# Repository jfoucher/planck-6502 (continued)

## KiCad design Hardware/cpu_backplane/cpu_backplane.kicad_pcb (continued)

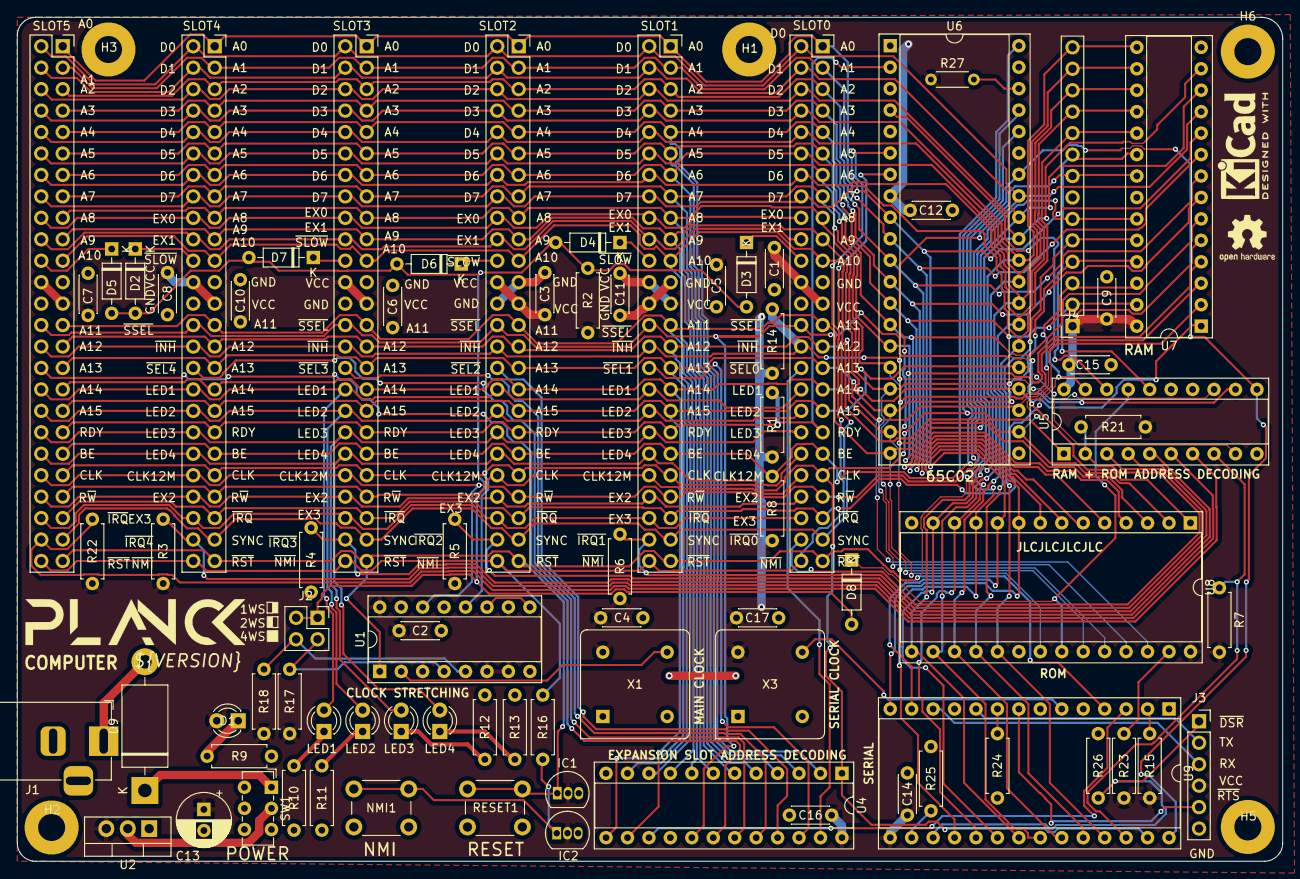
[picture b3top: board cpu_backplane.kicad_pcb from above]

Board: 2 copper layers, 149.9 x 99.9 mm, 85 parts (0 on the bottom side), 92 nets.

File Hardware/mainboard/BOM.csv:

Ref;Qnty;Value;Cmp name;Footprint;Description;Vendor
C1, C3, C7, C8, C10, C11,;6;1u;C_Small;Capacitor_THT:C_Disc_D4.3mm_W1.9mm_P5.00mm;Unpolarized capacitor, small symbol;
C2, C4, C5, C9, C12, C14, C15, C16, C17,;9;10n;C_Small;Capacitor_THT:C_Disc_D4.3mm_W1.9mm_P5.00mm;Unpolarized capacitor, small symbol;
C6,;1;47n;C_Small;Capacitor_THT:C_Disc_D4.3mm_W1.9mm_P5.00mm;Unpolarized capacitor, small symbol;
C13,;1;47u;C_Small;Capacitor_THT:CP_Radial_D6.3mm_P2.50mm;Unpolarized capacitor, small symbol;
D1,;1;LED;LED;LED_THT:LED_D3.0mm;Light emitting diode;
D2, D3, D4, D5, D6, D7, D8,;7;1N4148;D;Diode_THT:D_DO-35_SOD27_P7.62mm_Horizontal;Diode;
H1, H2, H3, H5, H6,;5;MountingHole_Pad;MountingHole_Pad;MountingHole:MountingHole_3.2mm_M3_Pad;Mounting Hole with connection;
J1,;1;USB_B_Micro;USB_B_Micro-Connector;Connector_USB:USB_Micro-B_Molex-105017-0001;;
J2,;1;Conn_02x02_Odd_Even;Conn_02x02_Odd_Even;Connector_PinHeader_2.54mm:PinHeader_2x02_P2.54mm_Vertical;Generic connector, double row, 02x02, odd/even pin numbering scheme (row 1 odd numbers, row 2 even numbers), script generated (kicad-library-utils/schlib/autogen/connector/);
J3,;1;Conn_01x06;Conn_01x06;Connector_PinSocket_2.54mm:PinSocket_1x06_P2.54mm_Vertical;Generic connector, single row, 01x06, script generated (kicad-library-utils/schlib/autogen/connector/);
J4,;1;Conn_01x14;Conn_01x14;Connector_PinSocket_2.54mm:PinSocket_1x14_P2.54mm_Vertical;Generic connector, single row, 01x14, script generated (kicad-library-utils/schlib/autogen/connector/);
LED1, LED2, LED3, LED4,;4;LED;LED;LED_THT:LED_D3.0mm;Light emitting diode;
NMI1,;1;SW_Push;SW_Push;Button_Switch_THT:SW_PUSH_6mm;Push button switch, generic, two pins;
R1, R8, R15, R23, R24, R25, R26,;7;10k;R_Small;Resistor_THT:R_Axial_DIN0207_L6.3mm_D2.5mm_P7.62mm_Horizontal;Resistor, small symbol;
R2, R3, R4, R5, R6, R14, R17, R18, R21, R22,;10;1k;R_Small;Resistor_THT:R_Axial_DIN0207_L6.3mm_D2.5mm_P7.62mm_Horizontal;Resistor, small symbol;
R9, R10, R11, R12, R13,;5;470R;R_Small;Resistor_THT:R_Axial_DIN0207_L6.3mm_D2.5mm_P7.62mm_Horizontal;Resistor, small symbol;
R16,;1;4.7k;R_Small;Resistor_THT:R_Axial_DIN0207_L6.3mm_D2.5mm_P7.62mm_Horizontal;Resistor, small symbol;
R27,;1;10k;R_Small;Resistor_THT:R_Axial_DIN0204_L3.6mm_D1.6mm_P5.08mm_Horizontal;Resistor, small symbol;
RESET1,;1;SW_Push;SW_Push;Button_Switch_THT:SW_PUSH_6mm;Push button switch, generic, two pins;
SLOT0, SLOT1, SLOT2, SLOT3, SLOT4, SLOT5,;6;Conn_01x40;Conn_02x25_Odd_Even;Connector_PinSocket_2.54mm:PinSocket_2x25_P2.54mm_Vertical;Generic connector, double row, 02x25, odd/even pin numbering scheme (row 1 odd numbers, row 2 even numbers), script generated (kicad-library-utils/schlib/autogen/connector/);
SW1,;1;SW_SPST;SW_SPST;Button_Switch_THT:SW_E-Switch_EG1271_DPDT;Single Pole Single Throw (SPST) switch;
U1,;1;74AC161;74LS161;Package_DIP:DIP-16_W7.62mm_Socket;Synchronous 4-bit programmable binary Counter;
U2, U3,;2;MAX811SEUS-T;MAX811SEUS-T;Package_TO_SOT_SMD:SOT-143;Power supply supervisor, Manual reset, Threshold 2.93V, SOT-143;
U4,;1;PAL24;PAL24;Package_DIP:DIP-24_W7.62mm_Socket;generic 24-pin Programmable Array Logic (PAL) device;
U5,;1;GAL16V8;GAL16V8;Package_DIP:DIP-20_W7.62mm_Socket;Programmable Logic Array, DIP-20/SOIC-20/PLCC-20;
U6,;1;W65C02SxP;W65C02SxP;Package_DIP:DIP-40_W15.24mm_Socket;W65C02S 8-bit CMOS General Purpose Microprocessor, DIP-40;
U7,;1;HM62256BLP;HM62256BLP;Package_DIP:DIP-28_W7.62mm_Socket;32,768-word × 8-bit High Speed CMOS Static RAM, 70ns, DIP-28;
U8,;1;28C256;28C256;Package_DIP:DIP-28_W15.24mm_Socket;Paged Parallel EEPROM 256Kb (32K x 8), DIP-28/SOIC-28;
U9,;1;W65C51NxP;W65C51NxP;Package_DIP:DIP-28_W15.24mm_Socket;W65C51N CMOS Asynchronous Communication Interface Adapter (ACIA), Serial UART, DIP-28;
X1,;1;24MHz;CXO_DIP8;Oscillator:Oscillator_DIP-8;Crystal Clock Oscillator, DIP8-style metal package;
X3,;1;1.8432MHz;CXO_DIP8;Oscillator:Oscillator_DIP-8;Crystal Clock Oscillator, DIP8-style metal package;

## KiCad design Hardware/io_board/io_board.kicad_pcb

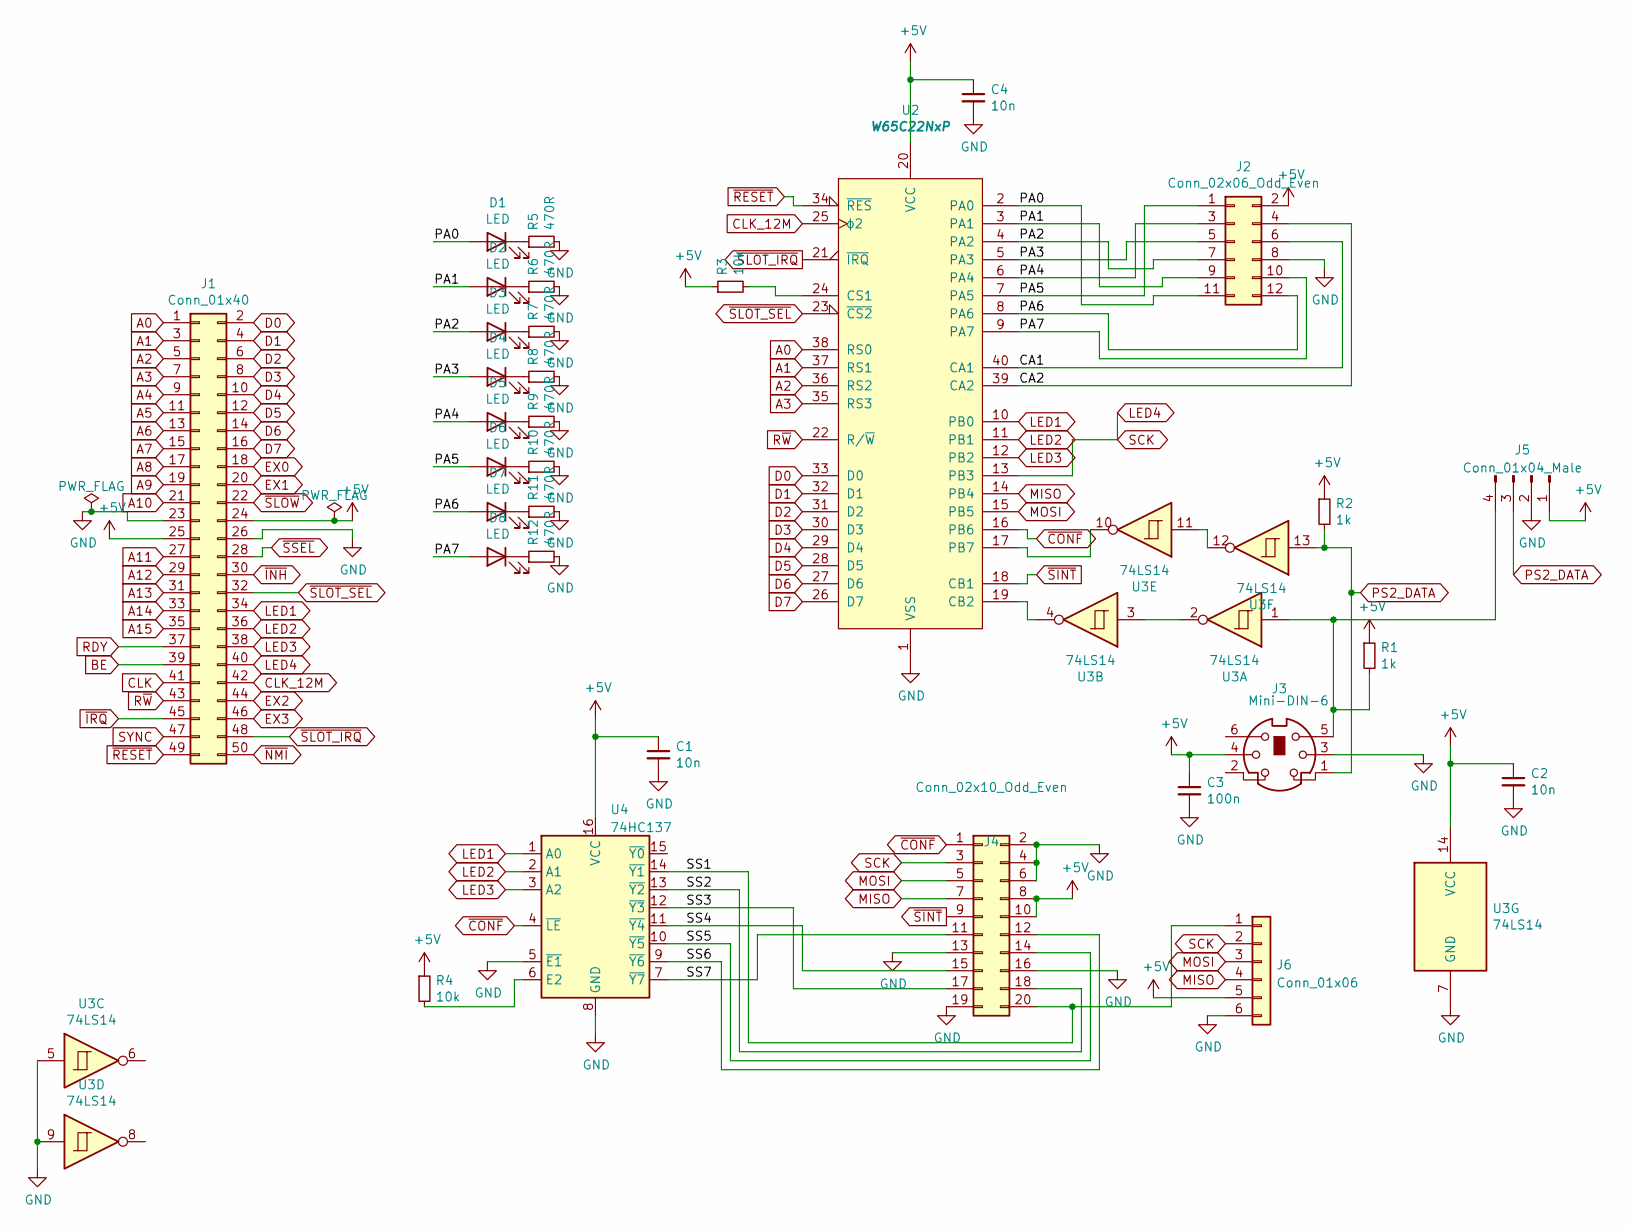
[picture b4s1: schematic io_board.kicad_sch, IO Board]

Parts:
C1, C2, C4: 10n; C_Disc_D4.7mm_W2.5mm_P5.00mm
C3: 100n; C_Disc_D4.7mm_W2.5mm_P5.00mm
D1, D2, D3, D4, D5, D6, D7, D8: LED; LED_D3.0mm_Horizontal_O3.81mm_Z6.0mm_2
J1: Conn_01x40; PinHeader_2x25_P2.54mm_Horizontal
J2: Conn_02x06_Odd_Even; PinHeader_2x06_P2.54mm_Horizontal
J3: Mini-DIN-6; Connector_Mini-DIN_Female_6Pin_2rows
J4: Conn_02x10_Odd_Even; PinHeader_2x10_P2.54mm_Horizontal
J5: Conn_01x04_Male; PinHeader_1x04_P2.54mm_Vertical
J6: Conn_01x06; PinSocket_1x06_P2.54mm_Vertical
R1, R2: 1k; R_Axial_DIN0207_L6.3mm_D2.5mm_P7.62mm_Horizontal
R3, R4: 10k; R_Axial_DIN0207_L6.3mm_D2.5mm_P7.62mm_Horizontal
R5, R6, R7, R8, R9, R10, R11, R12: 470R; R_Axial_DIN0207_L6.3mm_D2.5mm_P7.62mm_Horizontal
U2: W65C22NxP; DIP-40_W15.24mm_Socket
U3: 74LS14; DIP-14_W7.62mm_Socket
U4: 74HC137; DIP-16_W7.62mm_Socket

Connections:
+5V: C1.1, C2.1, C3.1, C4.1, J1.24, J1.25, J2.2, J3.4, J4.8, J4.10, J5.1, J6.5, R1.1, R2.1, R3.1, R4.1, U2.20 (VCC), U3.14 (VCC), U4.16 (VCC)
/CA1: J2.6, U2.40 (CA1)
/CA2: J2.4, U2.39 (CA2)
/PA0: D1.2 (A), J2.11, U2.2 (PA0)
/PA1: D2.2 (A), J2.9, U2.3 (PA1)
/PA2: D3.2 (A), J2.7, U2.4 (PA2)
/PA3: D4.2 (A), J2.5, U2.5 (PA3)
/PA4: D5.2 (A), J2.3, U2.6 (PA4)
/PA5: D6.2 (A), J2.1, U2.7 (PA5)
/PA6: D7.2 (A), J2.12, U2.8 (PA6)
/PA7: D8.2 (A), J2.10, U2.9 (PA7)
/SS1: J4.20, J6.1, U4.14 (~Y1)
/SS2: J4.18, U4.13 (~Y2)
/SS3: J4.17, U4.12 (~Y3)
/SS4: J4.15, U4.11 (~Y4)
/SS5: J4.14, U4.10 (~Y5)
/SS6: J4.12, U4.9 (~Y6)
/SS7: J4.11, U4.7 (~Y7)
A0: J1.1, U2.38 (RS0)
A1: J1.3, U2.37 (RS1)
A2: J1.5, U2.36 (RS2)
A3: J1.7, U2.35 (RS3)
A4: J1.9
A5: J1.11
A6: J1.13
A7: J1.15
A8: J1.17
A9: J1.19
A10: J1.21
A11: J1.27
A12: J1.29
A13: J1.31
A14: J1.33
A15: J1.35
BE: J1.39
CLK: J1.41
CLK_12M: J1.42, U2.25 (ϕ2)
D0: J1.2, U2.33 (D0)
D1: J1.4, U2.32 (D1)
D2: J1.6, U2.31 (D2)
D3: J1.8, U2.30 (D3)
D4: J1.10, U2.29 (D4)
D5: J1.12, U2.28 (D5)
D6: J1.14, U2.27 (D6)
D7: J1.16, U2.26 (D7)
EX0: J1.18
EX1: J1.20
EX2: J1.44
EX3: J1.46
GND: C1.2, C2.2, C3.2, C4.2, J1.23, J1.26, J2.8, J3.3, J4.2, J4.4, J4.6, J4.13, J4.16, J4.19, J5.2, J6.6, R5.2, R6.2, R7.2, R8.2, R9.2, R10.2, R11.2, R12.2, U2.1 (VSS), U3.5, U3.7 (GND), U3.9, U4.5 (~E1), U4.8 (GND)
LED1: J1.34, U2.10 (PB0), U4.1 (A0)
LED2: J1.36, U2.11 (PB1), U4.2 (A1)
LED3: J1.38, U2.12 (PB2), U4.3 (A2)
LED4: J1.40, J4.3, J6.2, U2.13 (PB3)
MISO: J4.7, J6.4, U2.14 (PB4)
MOSI: J4.5, J6.3, U2.15 (PB5)
unnamed: D1.1 (K), R5.1
unnamed: D2.1 (K), R6.1
unnamed: D3.1 (K), R7.1
unnamed: D4.1 (K), R8.1
unnamed: D5.1 (K), R9.1
unnamed: D6.1 (K), R10.1
unnamed: D7.1 (K), R11.1
unnamed: D8.1 (K), R12.1
unnamed: J3.5, J5.4, R1.2, U3.1
unnamed: R3.2, U2.24 (CS1)
unnamed: R4.2, U4.6 (E2)
unnamed: U2.17 (PB7), U3.10
unnamed: U2.19 (CB2), U3.4
unnamed: U3.2, U3.3
unnamed: U3.11, U3.12
PS2_DATA: J3.1, J5.3, R2.2, U3.13
RDY: J1.37
R~W: J1.43, U2.22 (R/~W)
SYNC: J1.47
~CONF: J4.1, U2.16 (PB6), U4.4 (~LE)
~INH: J1.30
~IRQ: J1.45
~NMI: J1.50
~RESET: J1.49, U2.34 (~RES)
~SINT: J4.9, U2.18 (CB1)
~SLOT_IRQ: J1.48, U2.21 (~IRQ)
~SLOT_SEL: J1.32, U2.23 (~CS2)
~SLOW: J1.22
~SSEL: J1.28

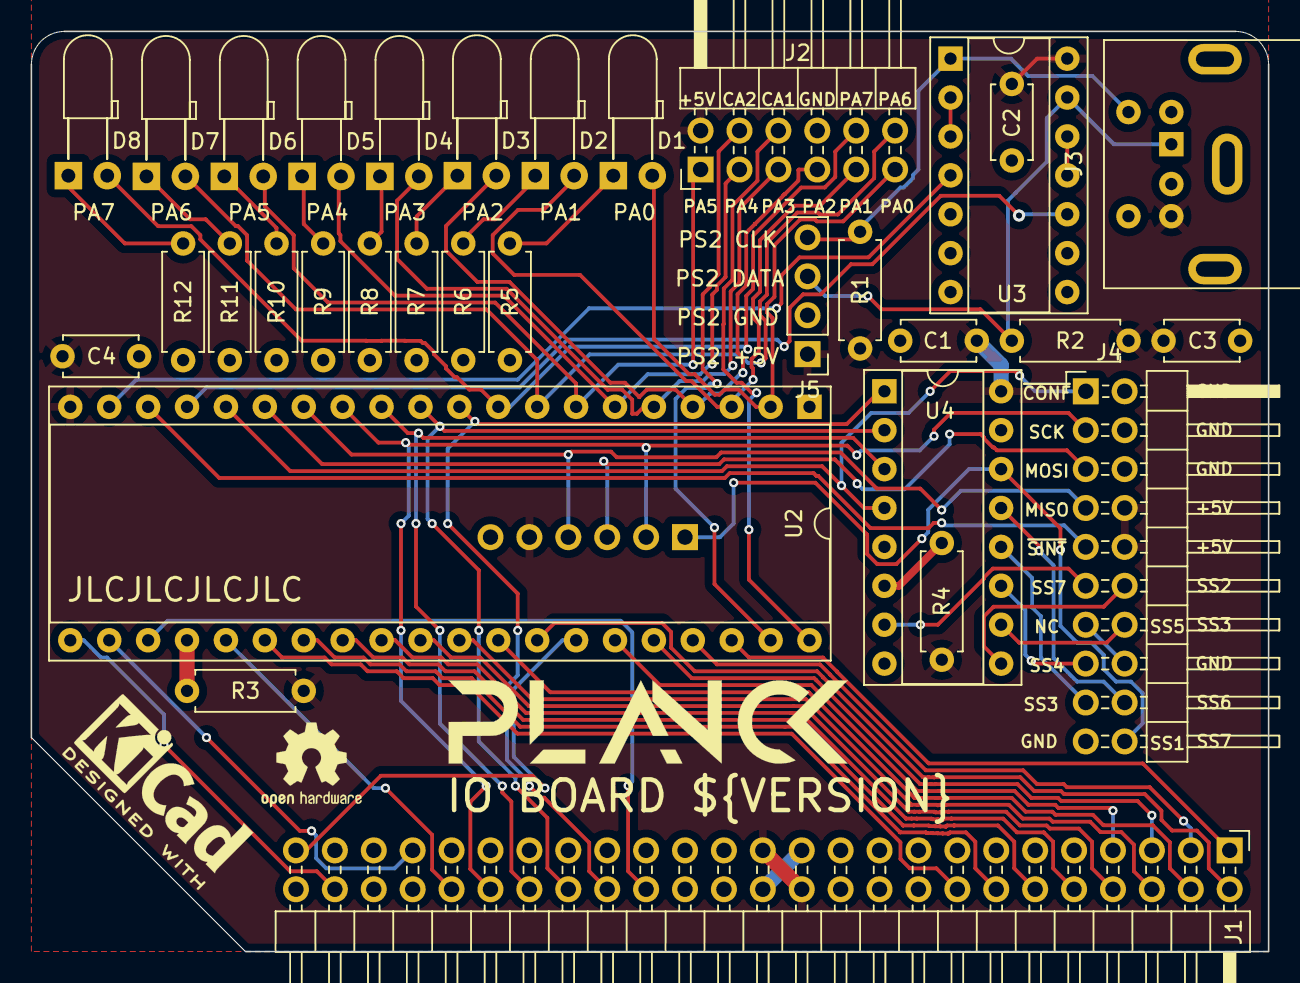
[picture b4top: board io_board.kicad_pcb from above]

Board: 2 copper layers, 80.8 x 60.1 mm, 33 parts (1 on the bottom side), 60 nets.

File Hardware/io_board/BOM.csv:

Ref;Qnty;Value;Cmp name;Footprint;Description;Vendor
C1, C2, C4,;3;10n;C_Small;Capacitor_THT:C_Disc_D4.7mm_W2.5mm_P5.00mm;Unpolarized capacitor, small symbol;
C3,;1;100n;C_Small;Capacitor_THT:C_Disc_D4.7mm_W2.5mm_P5.00mm;Unpolarized capacitor, small symbol;
D1, D2, D3, D4, D5, D6, D7, D8,;8;LED;LED;LED_THT:LED_D3.0mm_Horizontal_O3.81mm_Z6.0mm;Light emitting diode;
J1,;1;Conn_01x40;Conn_02x25_Odd_Even;Connector_PinHeader_2.54mm:PinHeader_2x25_P2.54mm_Horizontal;Generic connector, double row, 02x25, odd/even pin numbering scheme (row 1 odd numbers, row 2 even numbers);
J2,;1;Conn_02x06_Odd_Even;Conn_02x06_Odd_Even;Connector_PinHeader_2.54mm:PinHeader_2x06_P2.54mm_Horizontal;Generic connector, double row, 02x06, odd/even pin numbering scheme (row 1 odd numbers, row 2 even numbers);
J3,;1;Mini-DIN-6;Mini-DIN-6;mini-din:MINI-DIN-6-FULL-SHIELD;6-pin Mini-DIN connector;
J4,;1;Conn_02x10_Odd_Even;Conn_02x10_Odd_Even;Connector_PinHeader_2.54mm:PinHeader_2x10_P2.54mm_Horizontal;Generic connector, double row, 02x10, odd/even pin numbering scheme (row 1 odd numbers, row 2 even numbers);
R1, R2,;2;1k;R_Small;Resistor_THT:R_Axial_DIN0207_L6.3mm_D2.5mm_P7.62mm_Horizontal;Resistor, small symbol;
R3, R4,;2;10k;R_Small;Resistor_THT:R_Axial_DIN0207_L6.3mm_D2.5mm_P7.62mm_Horizontal;Resistor, small symbol;
R5, R6, R7, R8, R9, R10, R11, R12,;8;470R;R_Small;Resistor_THT:R_Axial_DIN0207_L6.3mm_D2.5mm_P7.62mm_Horizontal;Resistor, small symbol;
U1,;1;74LS138;74LS138;Package_DIP:DIP-16_W7.62mm_Socket;Decoder 3 to 8 active low outputs;
U2,;1;W65C22NxP;W65C22NxP;Package_DIP:DIP-40_W15.24mm_Socket;W65C22N CMOS Versatile Interface Adapter (VIA), 20-pin I/O, 2 Timer/Counters, NMOS-Compatible, DIP-40;
U3,;1;74LS14;74LS14;Package_DIP:DIP-14_W7.62mm_Socket;Hex inverter schmitt trigger;

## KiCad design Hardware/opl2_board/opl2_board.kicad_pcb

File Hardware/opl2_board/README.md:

## Planck 6502 sound card

This is a sound card based on the YM3892 OPL2 sound chip.

You can [download the schematic](https://planck6502.com/fabrication/opl2_board-schematic.pdf) and the [gerber files](https://planck6502.com/fabrication/opl2_board-zip.zip)

[Documentation](https://planck6502.com/Hardware/opl2/)

<br />This documentation is licensed under a <a rel="license" href="http://creativecommons.org/licenses/by-sa/4.0/">Creative Commons Attribution-ShareAlike 4.0 International License</a>.

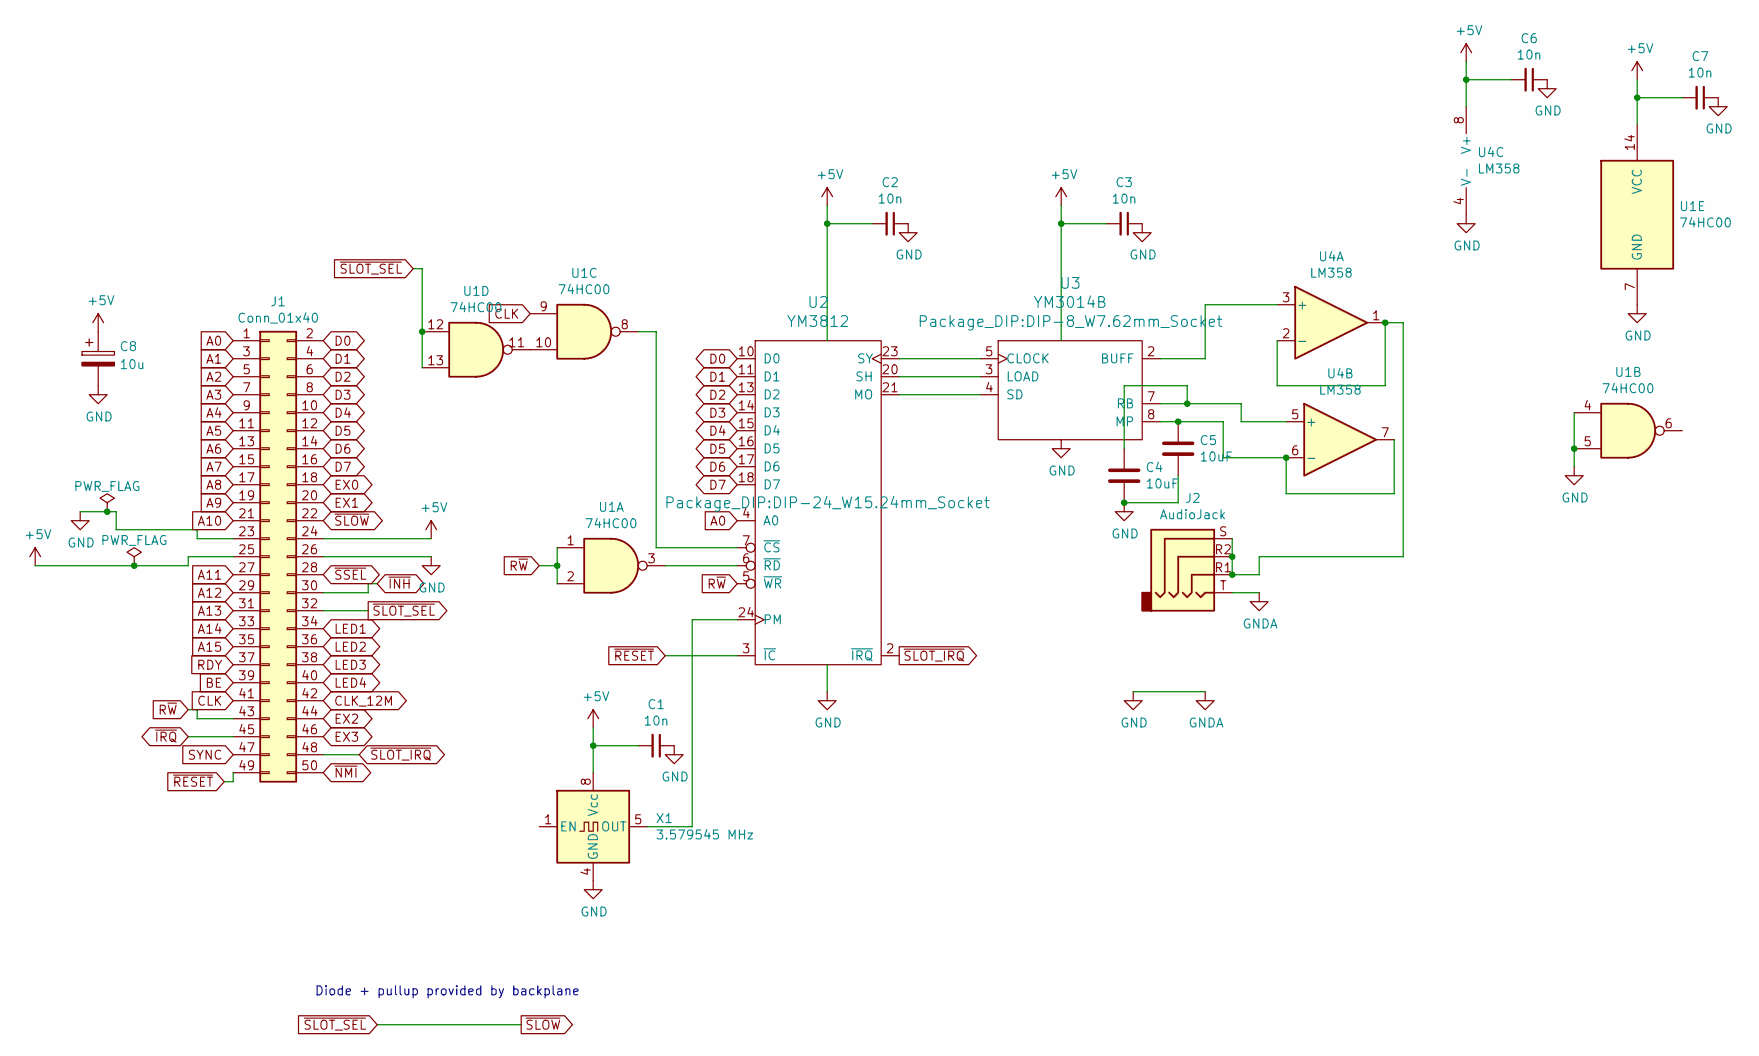
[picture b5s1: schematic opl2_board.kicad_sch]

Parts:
C1, C2, C3, C6, C7: 10n; C_Disc_D4.3mm_W1.9mm_P5.00mm
C4, C5: 10uF; C_Disc_D4.3mm_W1.9mm_P5.00mm
C8: 10u; CP_Radial_D5.0mm_P2.50mm
J1: Conn_01x40; PinHeader_2x25_P2.54mm_Horizontal
J2: AudioJack; TRRS-PJ-320A-no-Fmask
U1: 74HC00; DIP-14_W7.62mm_Socket
U2: YM3812; DIP-24_W15.24mm_Socket
U3: YM3014B; DIP-8_W7.62mm_Socket
U4: LM358; DIP-8_W7.62mm_Socket
X1: 3.579545 MHz; Oscillator_DIP-8

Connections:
+5V: C1.2, C2.2, C3.2, C6.2, C7.2, C8.1, J1.24, J1.25, U1.14 (VCC), U2.1 (VCC), U3.1 (VCC), U4.8 (V+), X1.8 (Vcc)
A0: J1.1, U2.4 (A0)
A1: J1.3
A2: J1.5
A3: J1.7
A4: J1.9
A5: J1.11
A6: J1.13
A7: J1.15
A8: J1.17
A9: J1.19
A10: J1.21
A11: J1.27
A12: J1.29
A13: J1.31
A14: J1.33
A15: J1.35
BE: J1.39
CLK: J1.41, U1.9
CLK_12M: J1.42
D0: J1.2, U2.10 (D0)
D1: J1.4, U2.11 (D1)
D2: J1.6, U2.13 (D2)
D3: J1.8, U2.14 (D3)
D4: J1.10, U2.15 (D4)
D5: J1.12, U2.16 (D5)
D6: J1.14, U2.17 (D6)
D7: J1.16, U2.18 (D7)
EX0: J1.18
EX1: J1.20
EX2: J1.44
EX3: J1.46
GND: C1.1, C2.1, C3.1, C4.2, C5.2, C6.1, C7.1, C8.2, J1.23, J1.26, J2.T, U1.4, U1.5, U1.7 (GND), U2.12 (GND), U3.6 (GND), U4.4 (V-), X1.4 (GND)
LED1: J1.34
LED2: J1.36
LED3: J1.38
LED4: J1.40
unnamed: C4.1, U3.7 (RB), U4.5 (+)
unnamed: C5.1, U3.8 (MP), U4.6 (-), U4.7
unnamed: J2.R1, J2.R2, J2.S, U4.1, U4.2 (-)
unnamed: U1.3, U2.6 (~RD)
unnamed: U1.8, U2.7 (~CS)
unnamed: U1.10, U1.11
unnamed: U2.20 (SH), U3.3 (LOAD)
unnamed: U2.21 (MO), U3.4 (SD)
unnamed: U2.23 (SY), U3.5 (CLOCK)
unnamed: U2.24 (PM), X1.5 (OUT)
unnamed: U3.2 (BUFF), U4.3 (+)
RDY: J1.37
R~W: J1.43, U1.1, U1.2, U2.5 (~WR)
SYNC: J1.47
~INH: J1.30
~IRQ: J1.45
~NMI: J1.50
~RESET: J1.49, U2.3 (~IC)
~SLOT_IRQ: J1.48, U2.2 (~IRQ)
~SLOT_SEL: J1.22, J1.32, U1.12, U1.13
~SSEL: J1.28

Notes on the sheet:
Diode + pullup provided by backplane

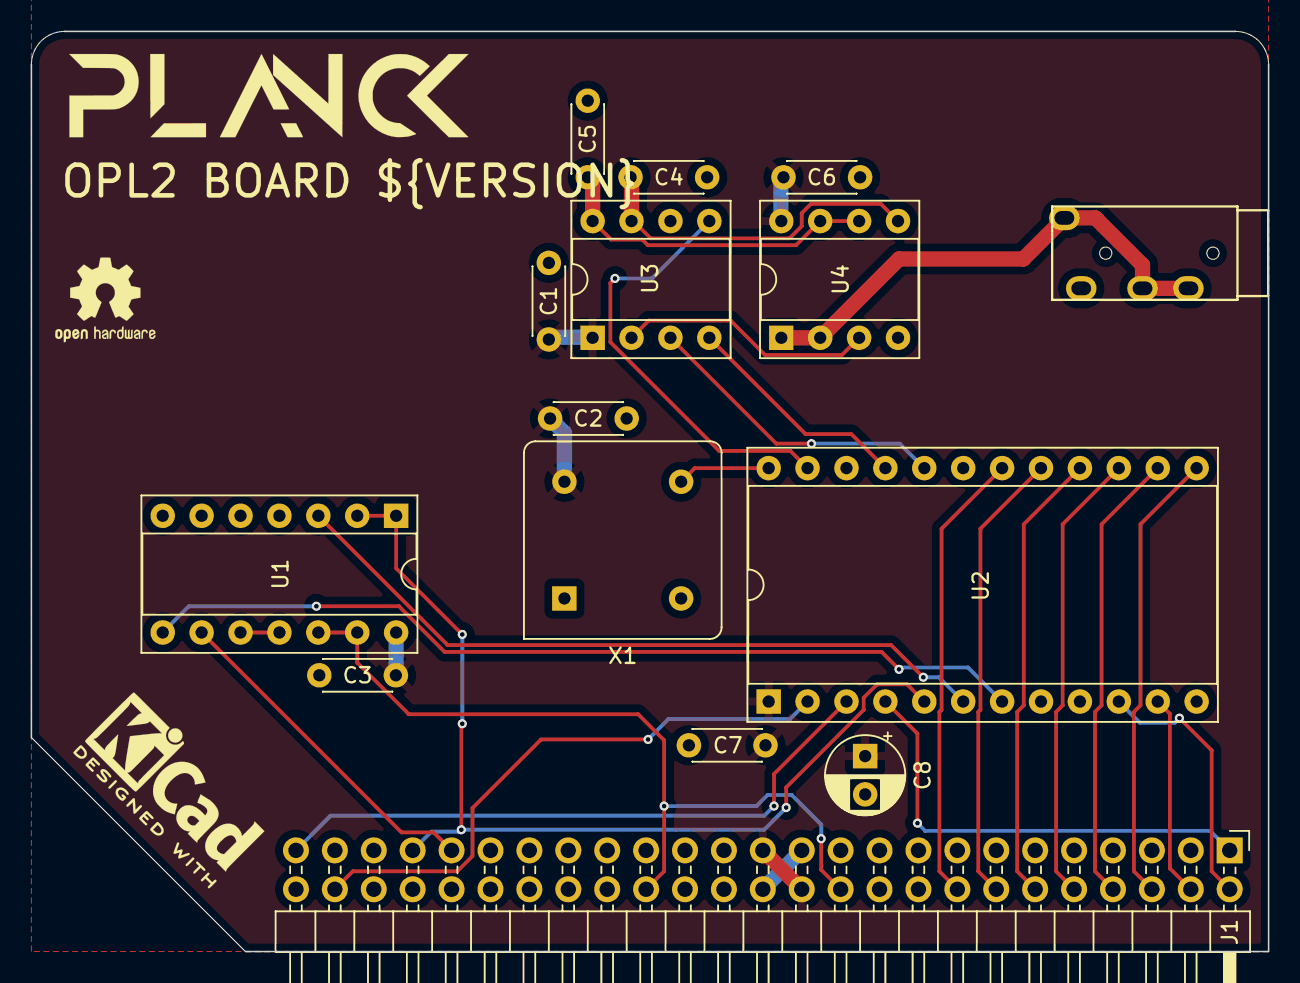
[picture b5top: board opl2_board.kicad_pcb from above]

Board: 2 copper layers, 80.8 x 60.1 mm, 15 parts (0 on the bottom side), 27 nets.

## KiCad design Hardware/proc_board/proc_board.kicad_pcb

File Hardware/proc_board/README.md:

## Planck CPU board

# Deprecated. Please use the [mainboard](../mainboard/) instead

This is the CPU board for the Planck 6502 based computer. It contains 32K of ram and 32K of rom.

The RAM and ROM can be inhibited by setting the <span style="text-decoration:overline">INH</span> signal low.

It is then the responsibility of that card to respond to the whole address range (execpt the one where expansion cards are active) to provide required functionality such as reset vectors, zero page, etc...

If the <span style="text-decoration:overline">SSEL</span> signal is low (one of the slots is active), both the RAM and the ROM will be offline.

The board can accept either a narrow or wide DIP28 RAM chip.

This is what the board looks like

<br />This documentation is licensed under a <a rel="license" href="http://creativecommons.org/licenses/by-sa/4.0/">Creative Commons Attribution-ShareAlike 4.0 International License</a>.

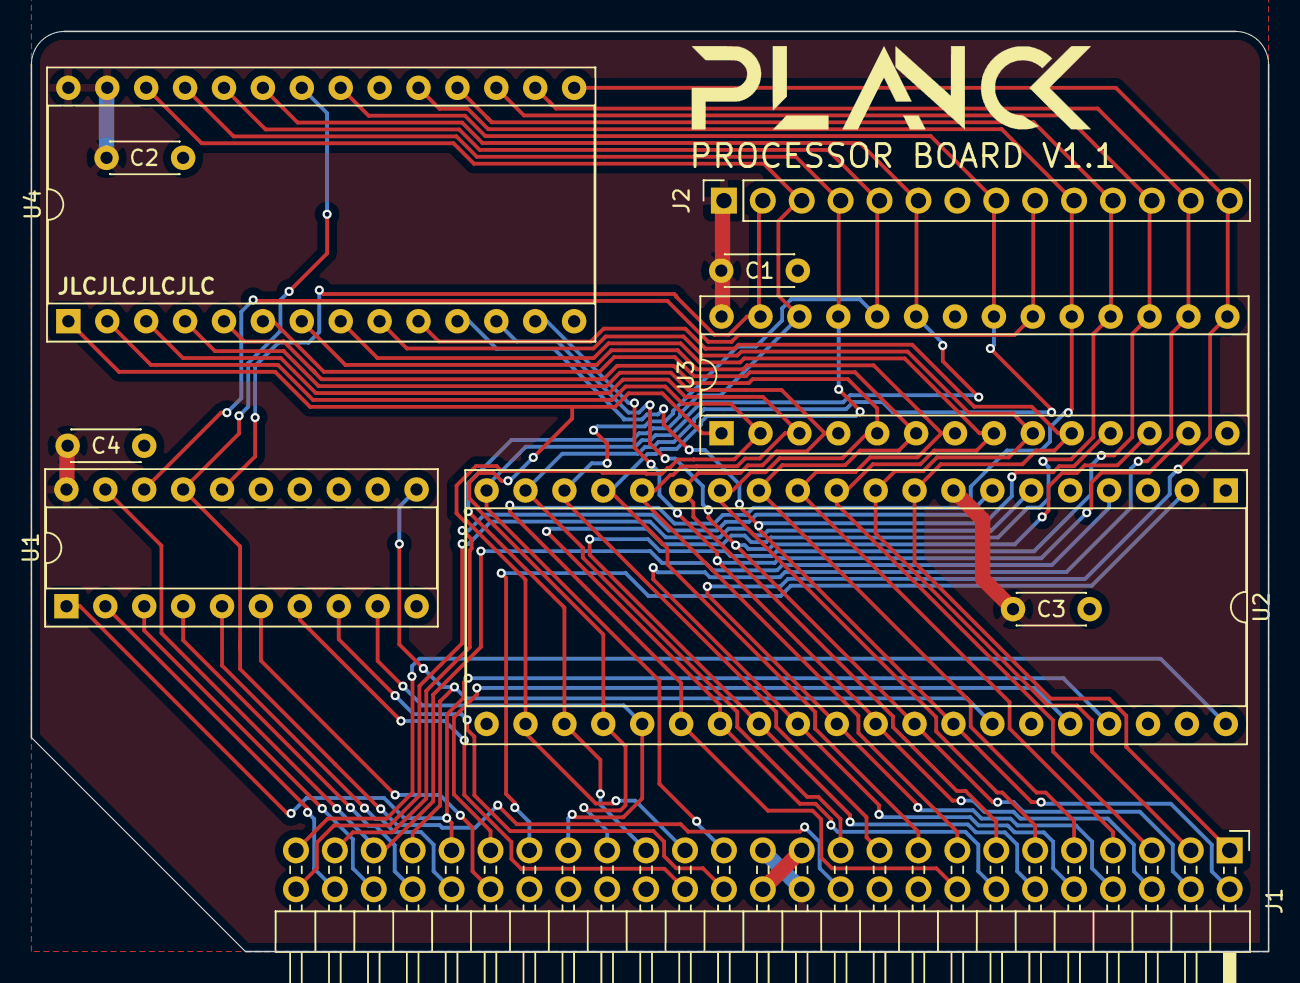
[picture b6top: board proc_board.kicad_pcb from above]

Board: 2 copper layers, 80.8 x 60.1 mm, 10 parts (0 on the bottom side), 44 nets.

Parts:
C1, C2, C3, C4: C_Small; C_Disc_D4.3mm_W1.9mm_P5.00mm
J1: Conn_01x40; PinHeader_2x25_P2.54mm_Horizontal
J2: Conn_01x14; PinSocket_1x14_P2.54mm_Vertical
U1: GAL16V8; DIP-20_W7.62mm_Socket
U2: W65C02SxP; DIP-40_W15.24mm_Socket
U3: HM62256BLP; DIP-28_W7.62mm_Socket
U4: 28C256; DIP-28_W15.24mm_Socket

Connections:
+5V: C1.2, C2.2, C3.2, C4.2, J1.24, J1.25, J2.1, U1.20, U2.8, U3.28, U4.27, U4.28
A0: J1.1, U2.9, U3.10, U4.10
A1: J1.3, U2.10, U3.9, U4.9
A2: J1.5, U2.11, U3.8, U4.8
A3: J1.7, U2.12, U3.7, U4.7
A4: J1.9, U2.13, U3.6, U4.6
A5: J1.11, U2.14, U3.5, U4.5
A6: J1.13, U2.15, U3.4, U4.4
A7: J1.15, U2.16, U3.3, U4.3
A8: J1.17, J2.4, U2.17, U3.25, U4.25
A9: J1.19, J2.5, U2.18, U3.24, U4.24
A10: J1.21, J2.8, U2.19, U3.21, U4.21
A11: J1.27, J2.6, U2.20, U3.23, U4.23
A12: J1.29, U2.22, U3.2, U4.2
A13: J1.31, J2.3, U2.23, U3.26, U4.26
A14: J1.33, U2.24, U3.1, U4.1
A15: J1.35, U1.9, U2.25
BE: J1.39, U2.36
CLK: J1.41, U1.1, U2.37
D0: J1.2, U2.33, U3.11, U4.11
D1: J1.4, U2.32, U3.12, U4.12
D2: J1.6, U2.31, U3.13, U4.13
D3: J1.8, J2.14, U2.30, U3.15, U4.15
D4: J1.10, J2.13, U2.29, U3.16, U4.16
D5: J1.12, J2.12, U2.28, U3.17, U4.17
D6: J1.14, J2.11, U2.27, U3.18, U4.18
D7: J1.16, J2.10, U2.26, U3.19, U4.19
GND: C1.1, C2.1, C3.1, C4.1, J1.23, J1.26, J2.7, U1.10, U2.21, U3.14, U3.22, U4.14, U4.20
RDY: J1.37, U2.2
R~W~: J1.43, U1.11, U2.34
SYNC: J1.47, U2.7
~INH~: J1.30, U1.7
~IRQ1~: J1.48, U1.2
~IRQ2~: J1.46, U1.3
~IRQ3~: J1.44, U1.4
~IRQ4~: J1.42, U1.5
~IRQ5~: J1.40, U1.6
~IRQ~: J1.45, U1.19, U2.4
~NMI~: J1.50, U2.6
~RAMW~: J2.2, U1.16, U3.27
~RAM_CS~: J2.9, U1.18, U3.20
~RESET~: J1.49, U2.40
~ROM_CS~: J1.22, U1.17, U4.22
~SSEL~: J1.28, U1.8
